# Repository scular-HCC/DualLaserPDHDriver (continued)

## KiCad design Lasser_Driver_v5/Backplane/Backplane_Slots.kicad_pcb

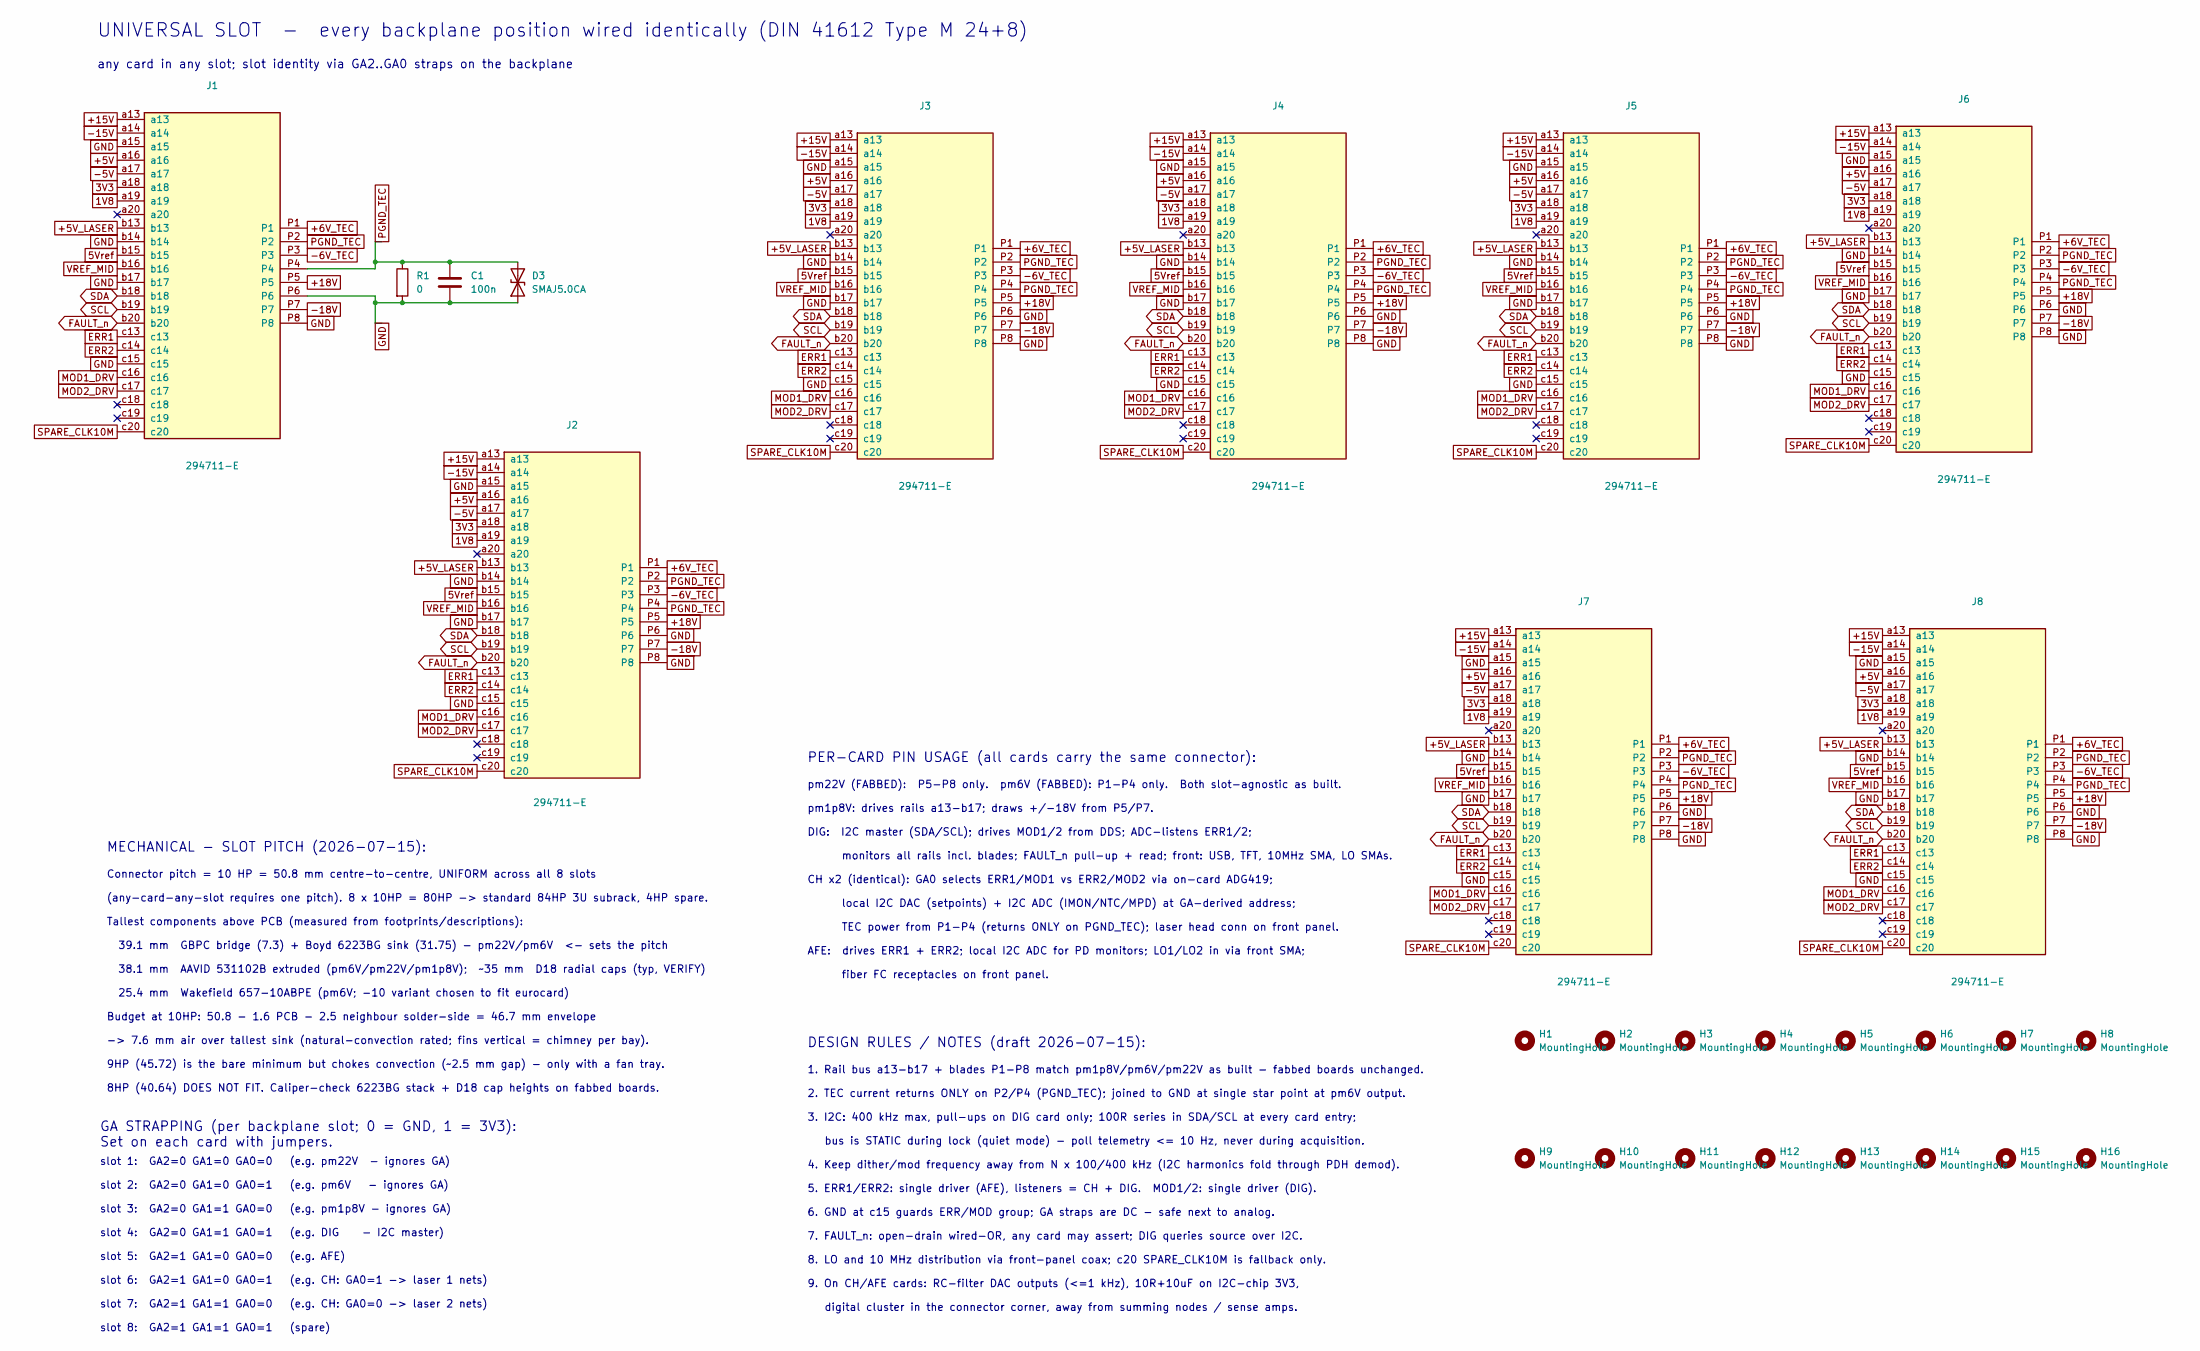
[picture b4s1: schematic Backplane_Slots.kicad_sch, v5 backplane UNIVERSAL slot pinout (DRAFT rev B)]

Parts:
C1: 100n; C_0805_2012Metric_Pad1.18x1.45mm_HandSolder
D3: SMAJ5.0CA; D_SMA-SMB_Universal_Handsoldering; MPN SMAJ5.0CA-E3/61
H1, H2, H3, H4, H5, H6, H7, H8, H9, H10, H11, H12, H13, H14, H15, H16: MountingHole; MountingHole_2.7mm
J1, J2, J3, J4, J5, J6, J7, J8: 294711-E; DIN41612_M_3x8+8_Female_Vertical_THT_Power
R1: 0; R_0805_2012Metric_Pad1.20x1.40mm_HandSolder

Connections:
1V8: J1.a19, J2.a19, J3.a19, J4.a19, J5.a19, J6.a19, J7.a19, J8.a19
3V3: J1.a18, J2.a18, J3.a18, J4.a18, J5.a18, J6.a18, J7.a18, J8.a18
5Vref: J1.b15, J2.b15, J3.b15, J4.b15, J5.b15, J6.b15, J7.b15, J8.b15
+5V: J1.a16, J2.a16, J3.a16, J4.a16, J5.a16, J6.a16, J7.a16, J8.a16
+5V_LASER: J1.b13, J2.b13, J3.b13, J4.b13, J5.b13, J6.b13, J7.b13, J8.b13
+6V_TEC: J1.P1, J2.P1, J3.P1, J4.P1, J5.P1, J6.P1, J7.P1, J8.P1
+15V: J1.a13, J2.a13, J3.a13, J4.a13, J5.a13, J6.a13, J7.a13, J8.a13
+18V: J1.P5, J2.P5, J3.P5, J4.P5, J5.P5, J6.P5, J7.P5, J8.P5
-5V: J1.a17, J2.a17, J3.a17, J4.a17, J5.a17, J6.a17, J7.a17, J8.a17
-6V_TEC: J1.P3, J2.P3, J3.P3, J4.P3, J5.P3, J6.P3, J7.P3, J8.P3
-15V: J1.a14, J2.a14, J3.a14, J4.a14, J5.a14, J6.a14, J7.a14, J8.a14
-18V: J1.P7, J2.P7, J3.P7, J4.P7, J5.P7, J6.P7, J7.P7, J8.P7
ERR1: J1.c13, J2.c13, J3.c13, J4.c13, J5.c13, J6.c13, J7.c13, J8.c13
ERR2: J1.c14, J2.c14, J3.c14, J4.c14, J5.c14, J6.c14, J7.c14, J8.c14
FAULT_n: J1.b20, J2.b20, J3.b20, J4.b20, J5.b20, J6.b20, J7.b20, J8.b20
GND: C1.2, D3.1 (A1), J1.P6, J1.P8, J1.a15, J1.b14, J1.b17, J1.c15, J2.P6, J2.P8, J2.a15, J2.b14, J2.b17, J2.c15, J3.P6, J3.P8, J3.a15, J3.b14, J3.b17, J3.c15, J4.P6, J4.P8, J4.a15, J4.b14, J4.b17, J4.c15, J5.P6, J5.P8, J5.a15, J5.b14, J5.b17, J5.c15, J6.P6, J6.P8, J6.a15, J6.b14, J6.b17, J6.c15, J7.P6, J7.P8, J7.a15, J7.b14, J7.b17, J7.c15, J8.P6, J8.P8, J8.a15, J8.b14, J8.b17, J8.c15, R1.2
MOD1_DRV: J1.c16, J2.c16, J3.c16, J4.c16, J5.c16, J6.c16, J7.c16, J8.c16
MOD2_DRV: J1.c17, J2.c17, J3.c17, J4.c17, J5.c17, J6.c17, J7.c17, J8.c17
PGND_TEC: C1.1, D3.2 (A2), J1.P2, J1.P4, J2.P2, J2.P4, J3.P2, J3.P4, J4.P2, J4.P4, J5.P2, J5.P4, J6.P2, J6.P4, J7.P2, J7.P4, J8.P2, J8.P4, R1.1
SCL: J1.b19, J2.b19, J3.b19, J4.b19, J5.b19, J6.b19, J7.b19, J8.b19
SDA: J1.b18, J2.b18, J3.b18, J4.b18, J5.b18, J6.b18, J7.b18, J8.b18
SPARE_CLK10M: J1.c20, J2.c20, J3.c20, J4.c20, J5.c20, J6.c20, J7.c20, J8.c20
VREF_MID: J1.b16, J2.b16, J3.b16, J4.b16, J5.b16, J6.b16, J7.b16, J8.b16

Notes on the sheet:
pm22V (FABBED): P5-P8 only. pm6V (FABBED): P1-P4 only. Both slot-agnostic as built.
DIG: I2C master (SDA/SCL); drives MOD1/2 from DDS; ADC-listens ERR1/2;
2. TEC current returns ONLY on P2/P4 (PGND_TEC); joined to GND at single star point at pm6V output.
8. LO and 10 MHz distribution via front-panel coax; c20 SPARE_CLK10M is fallback only.
AFE: drives ERR1 + ERR2; local I2C ADC for PD monitors; LO1/LO2 in via front SMA;
6. GND at c15 guards ERR/MOD group; GA straps are DC - safe next to analog.
38.1 mm AAVID 531102B extruded (pm6V/pm22V/pm1p8V); ~35 mm D18 radial caps (typ, VERIFY)
TEC power from P1-P4 (returns ONLY on PGND_TEC); laser head conn on front panel.
slot 5: GA2=1 GA1=0 GA0=0 (e.g. AFE)
slot 3: GA2=0 GA1=1 GA0=0 (e.g. pm1p8V - ignores GA)
PER-CARD PIN USAGE (all cards carry the same connector):
any card in any slot; slot identity via GA2..GA0 straps on the backplane
Budget at 10HP: 50.8 - 1.6 PCB - 2.5 neighbour solder-side = 46.7 mm envelope
(any-card-any-slot requires one pitch). 8 x 10HP = 80HP -> standard 84HP 3U subrack, 4HP spare.
1. Rail bus a13-b17 + blades P1-P8 match pm1p8V/pm6V/pm22V as built - fabbed boards unchanged.
slot 6: GA2=1 GA1=0 GA0=1 (e.g. CH: GA0=1 -> laser 1 nets)
slot 7: GA2=1 GA1=1 GA0=0 (e.g. CH: GA0=0 -> laser 2 nets)
bus is STATIC during lock (quiet mode) - poll telemetry <= 10 Hz, never during acquisition.
8HP (40.64) DOES NOT FIT. Caliper-check 6223BG stack + D18 cap heights on fabbed boards.
slot 4: GA2=0 GA1=1 GA0=1 (e.g. DIG - I2C master)
4. Keep dither/mod frequency away from N x 100/400 kHz (I2C harmonics fold through PDH demod).
slot 8: GA2=1 GA1=1 GA0=1 (spare)
Tallest components above PCB (measured from footprints/descriptions):
MECHANICAL - SLOT PITCH (2026-07-15):
GA STRAPPING (per backplane slot; 0 = GND, 1 = 3V3): Set on each card with jumpers.
local I2C DAC (setpoints) + I2C ADC (IMON/NTC/MPD) at GA-derived address;
39.1 mm GBPC bridge (7.3) + Boyd 6223BG sink (31.75) - pm22V/pm6V <- sets the pitch
DESIGN RULES / NOTES (draft 2026-07-15):
25.4 mm Wakefield 657-10ABPE (pm6V; -10 variant chosen to fit eurocard)
9. On CH/AFE cards: RC-filter DAC outputs (<=1 kHz), 10R+10uF on I2C-chip 3V3,
digital cluster in the connector corner, away from summing nodes / sense amps.
-> 7.6 mm air over tallest sink (natural-convection rated; fins vertical = chimney per bay).
7. FAULT_n: open-drain wired-OR, any card may assert; DIG queries source over I2C.
Connector pitch = 10 HP = 50.8 mm centre-to-centre, UNIFORM across all 8 slots
slot 2: GA2=0 GA1=0 GA0=1 (e.g. pm6V - ignores GA)
monitors all rails incl. blades; FAULT_n pull-up + read; front: USB, TFT, 10MHz SMA, LO SMAs.
CH x2 (identical): GA0 selects ERR1/MOD1 vs ERR2/MOD2 via on-card ADG419;
slot 1: GA2=0 GA1=0 GA0=0 (e.g. pm22V - ignores GA)
UNIVERSAL SLOT - every backplane position wired identically (DIN 41612 Type M 24+8)
fiber FC receptacles on front panel.

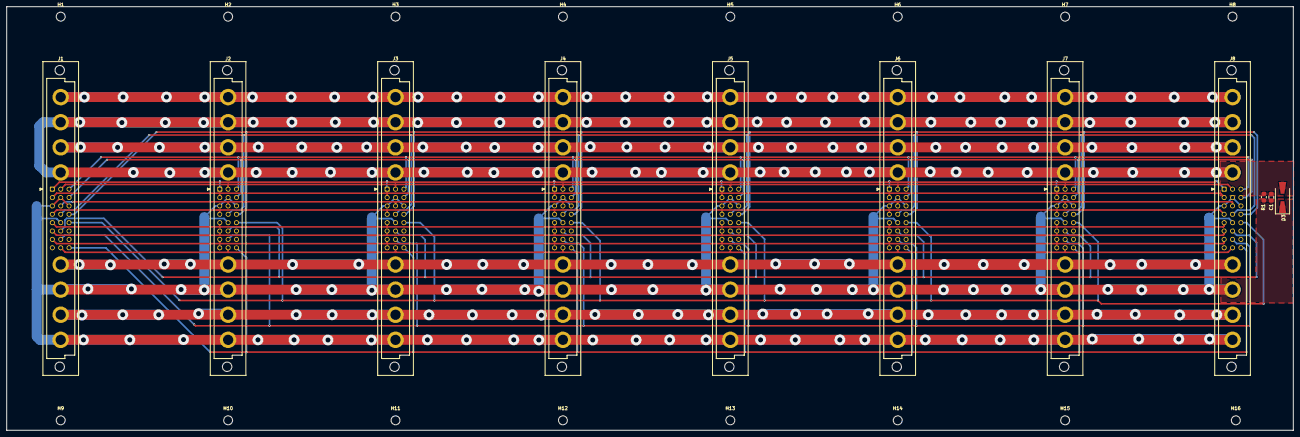
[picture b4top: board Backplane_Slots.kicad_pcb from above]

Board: 2 copper layers, 390.4 x 128.6 mm, 27 parts (0 on the bottom side), 23 nets.

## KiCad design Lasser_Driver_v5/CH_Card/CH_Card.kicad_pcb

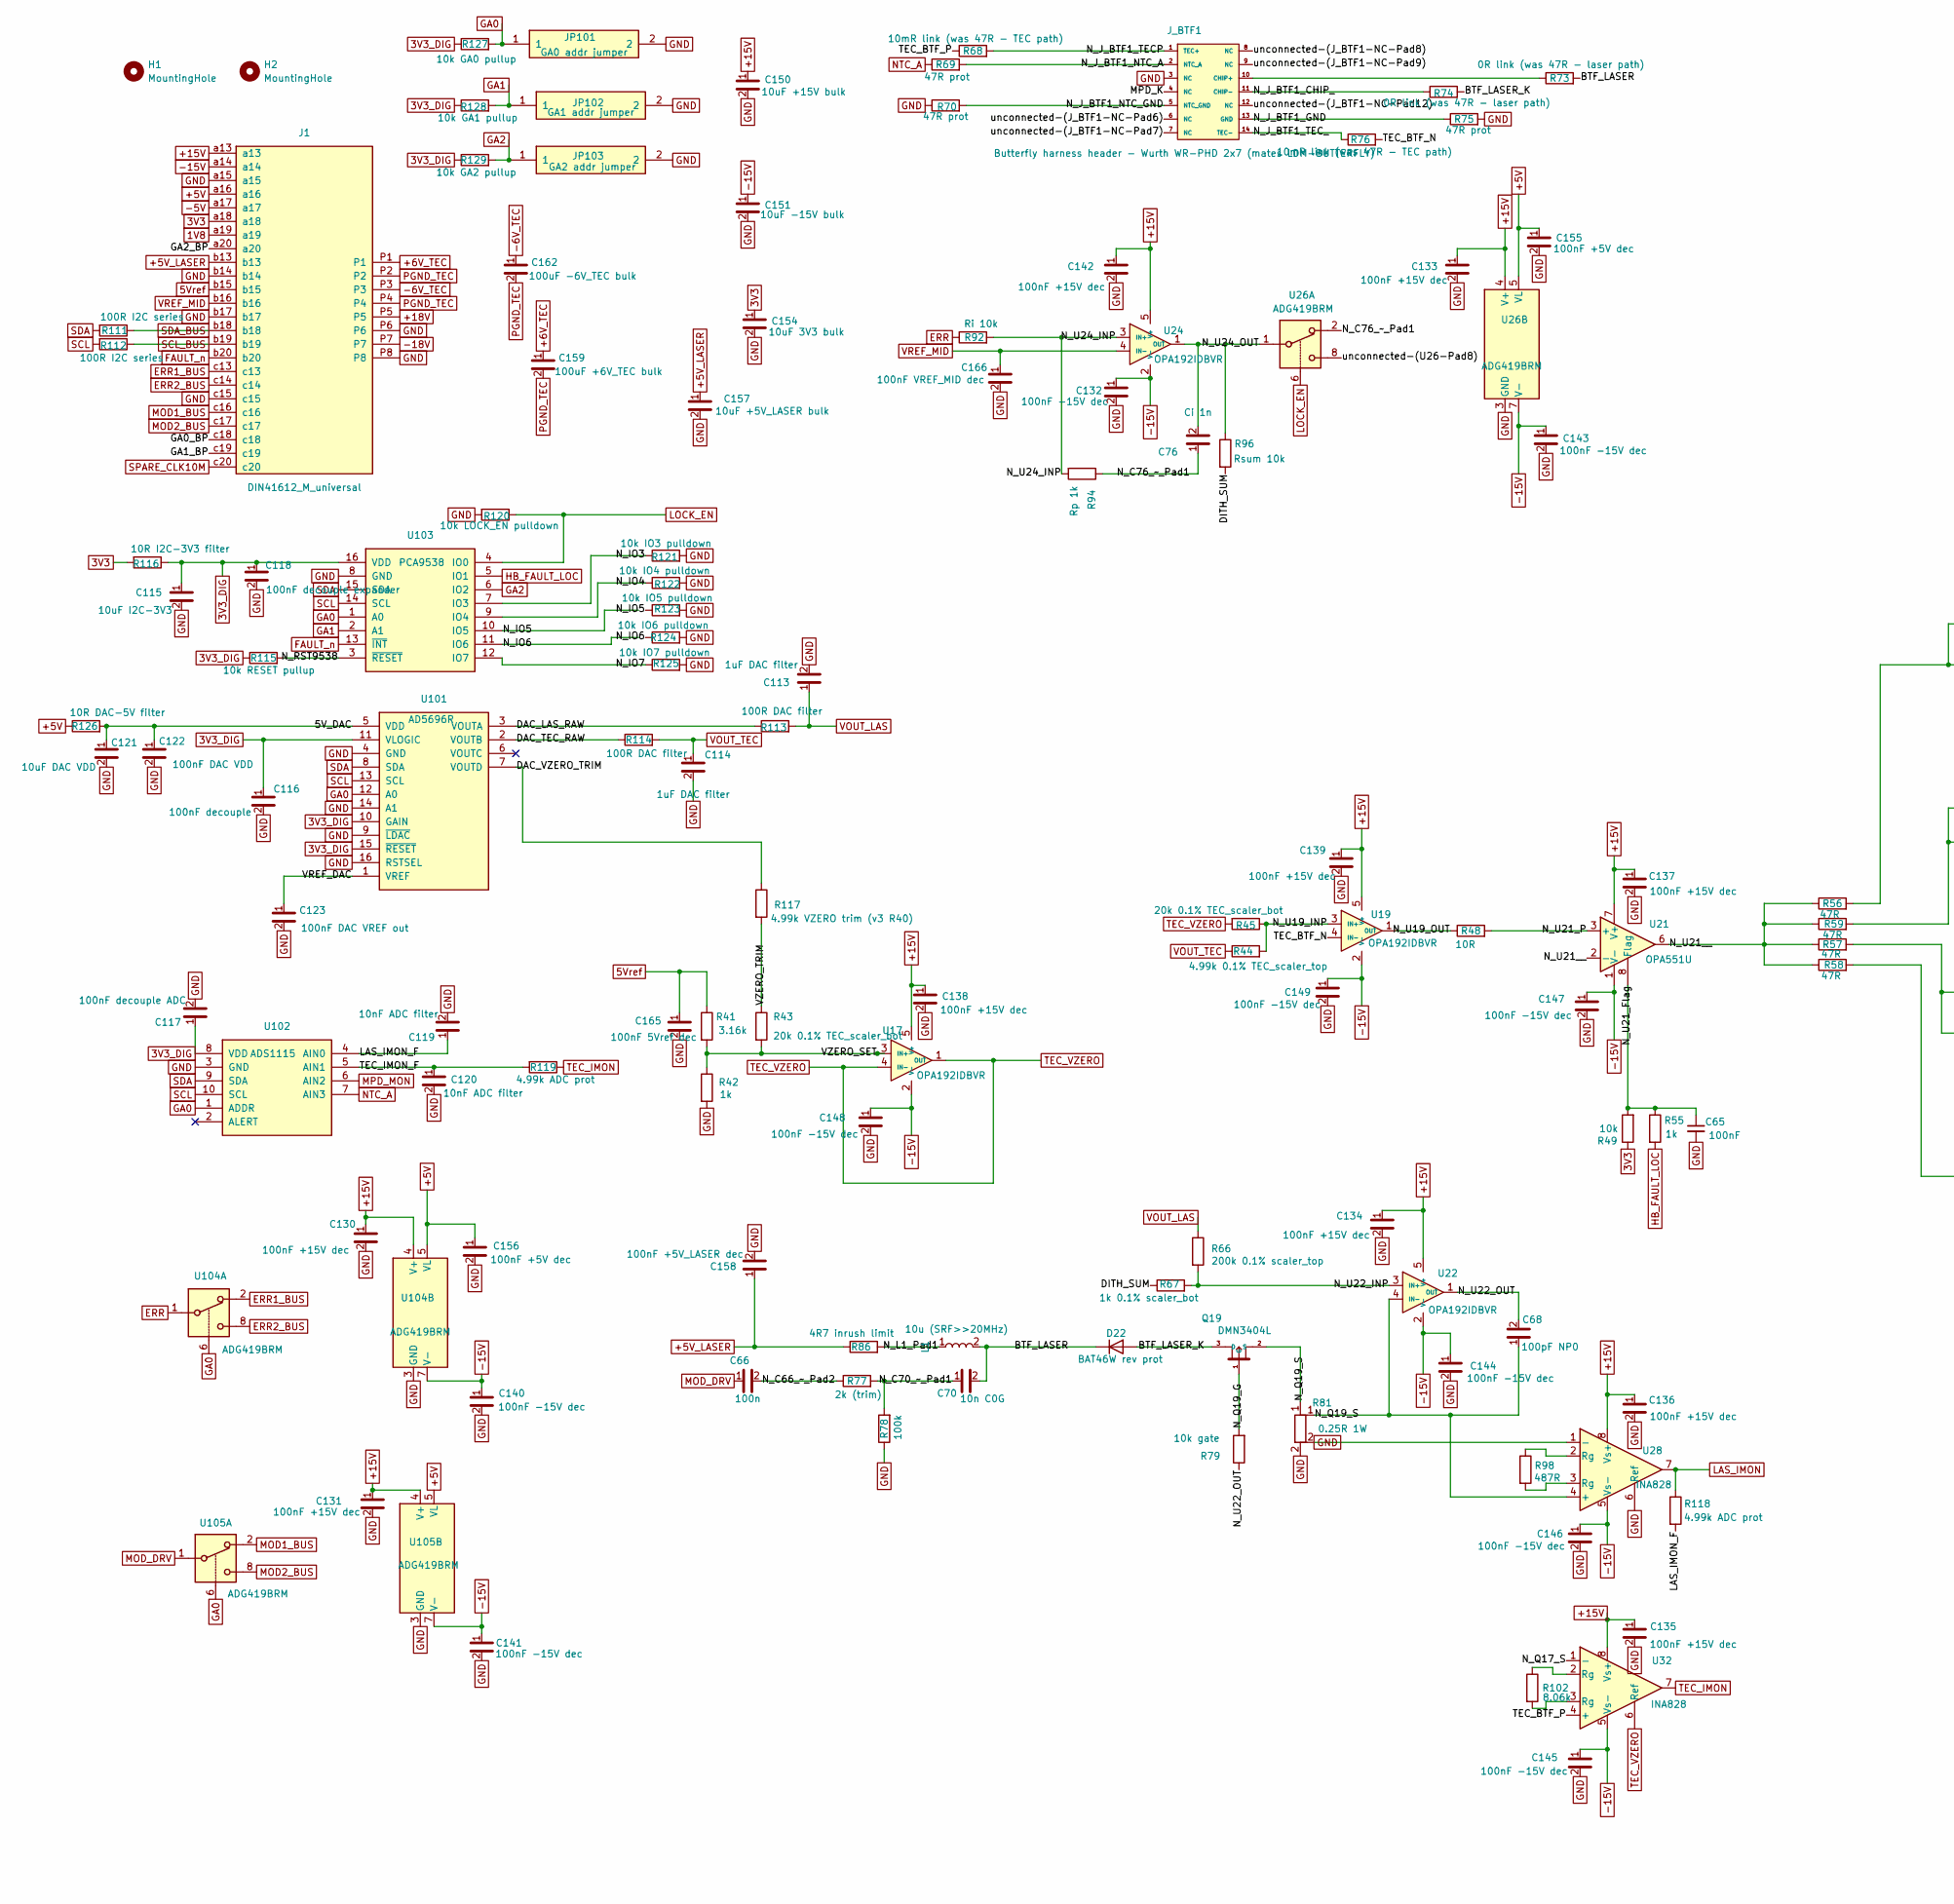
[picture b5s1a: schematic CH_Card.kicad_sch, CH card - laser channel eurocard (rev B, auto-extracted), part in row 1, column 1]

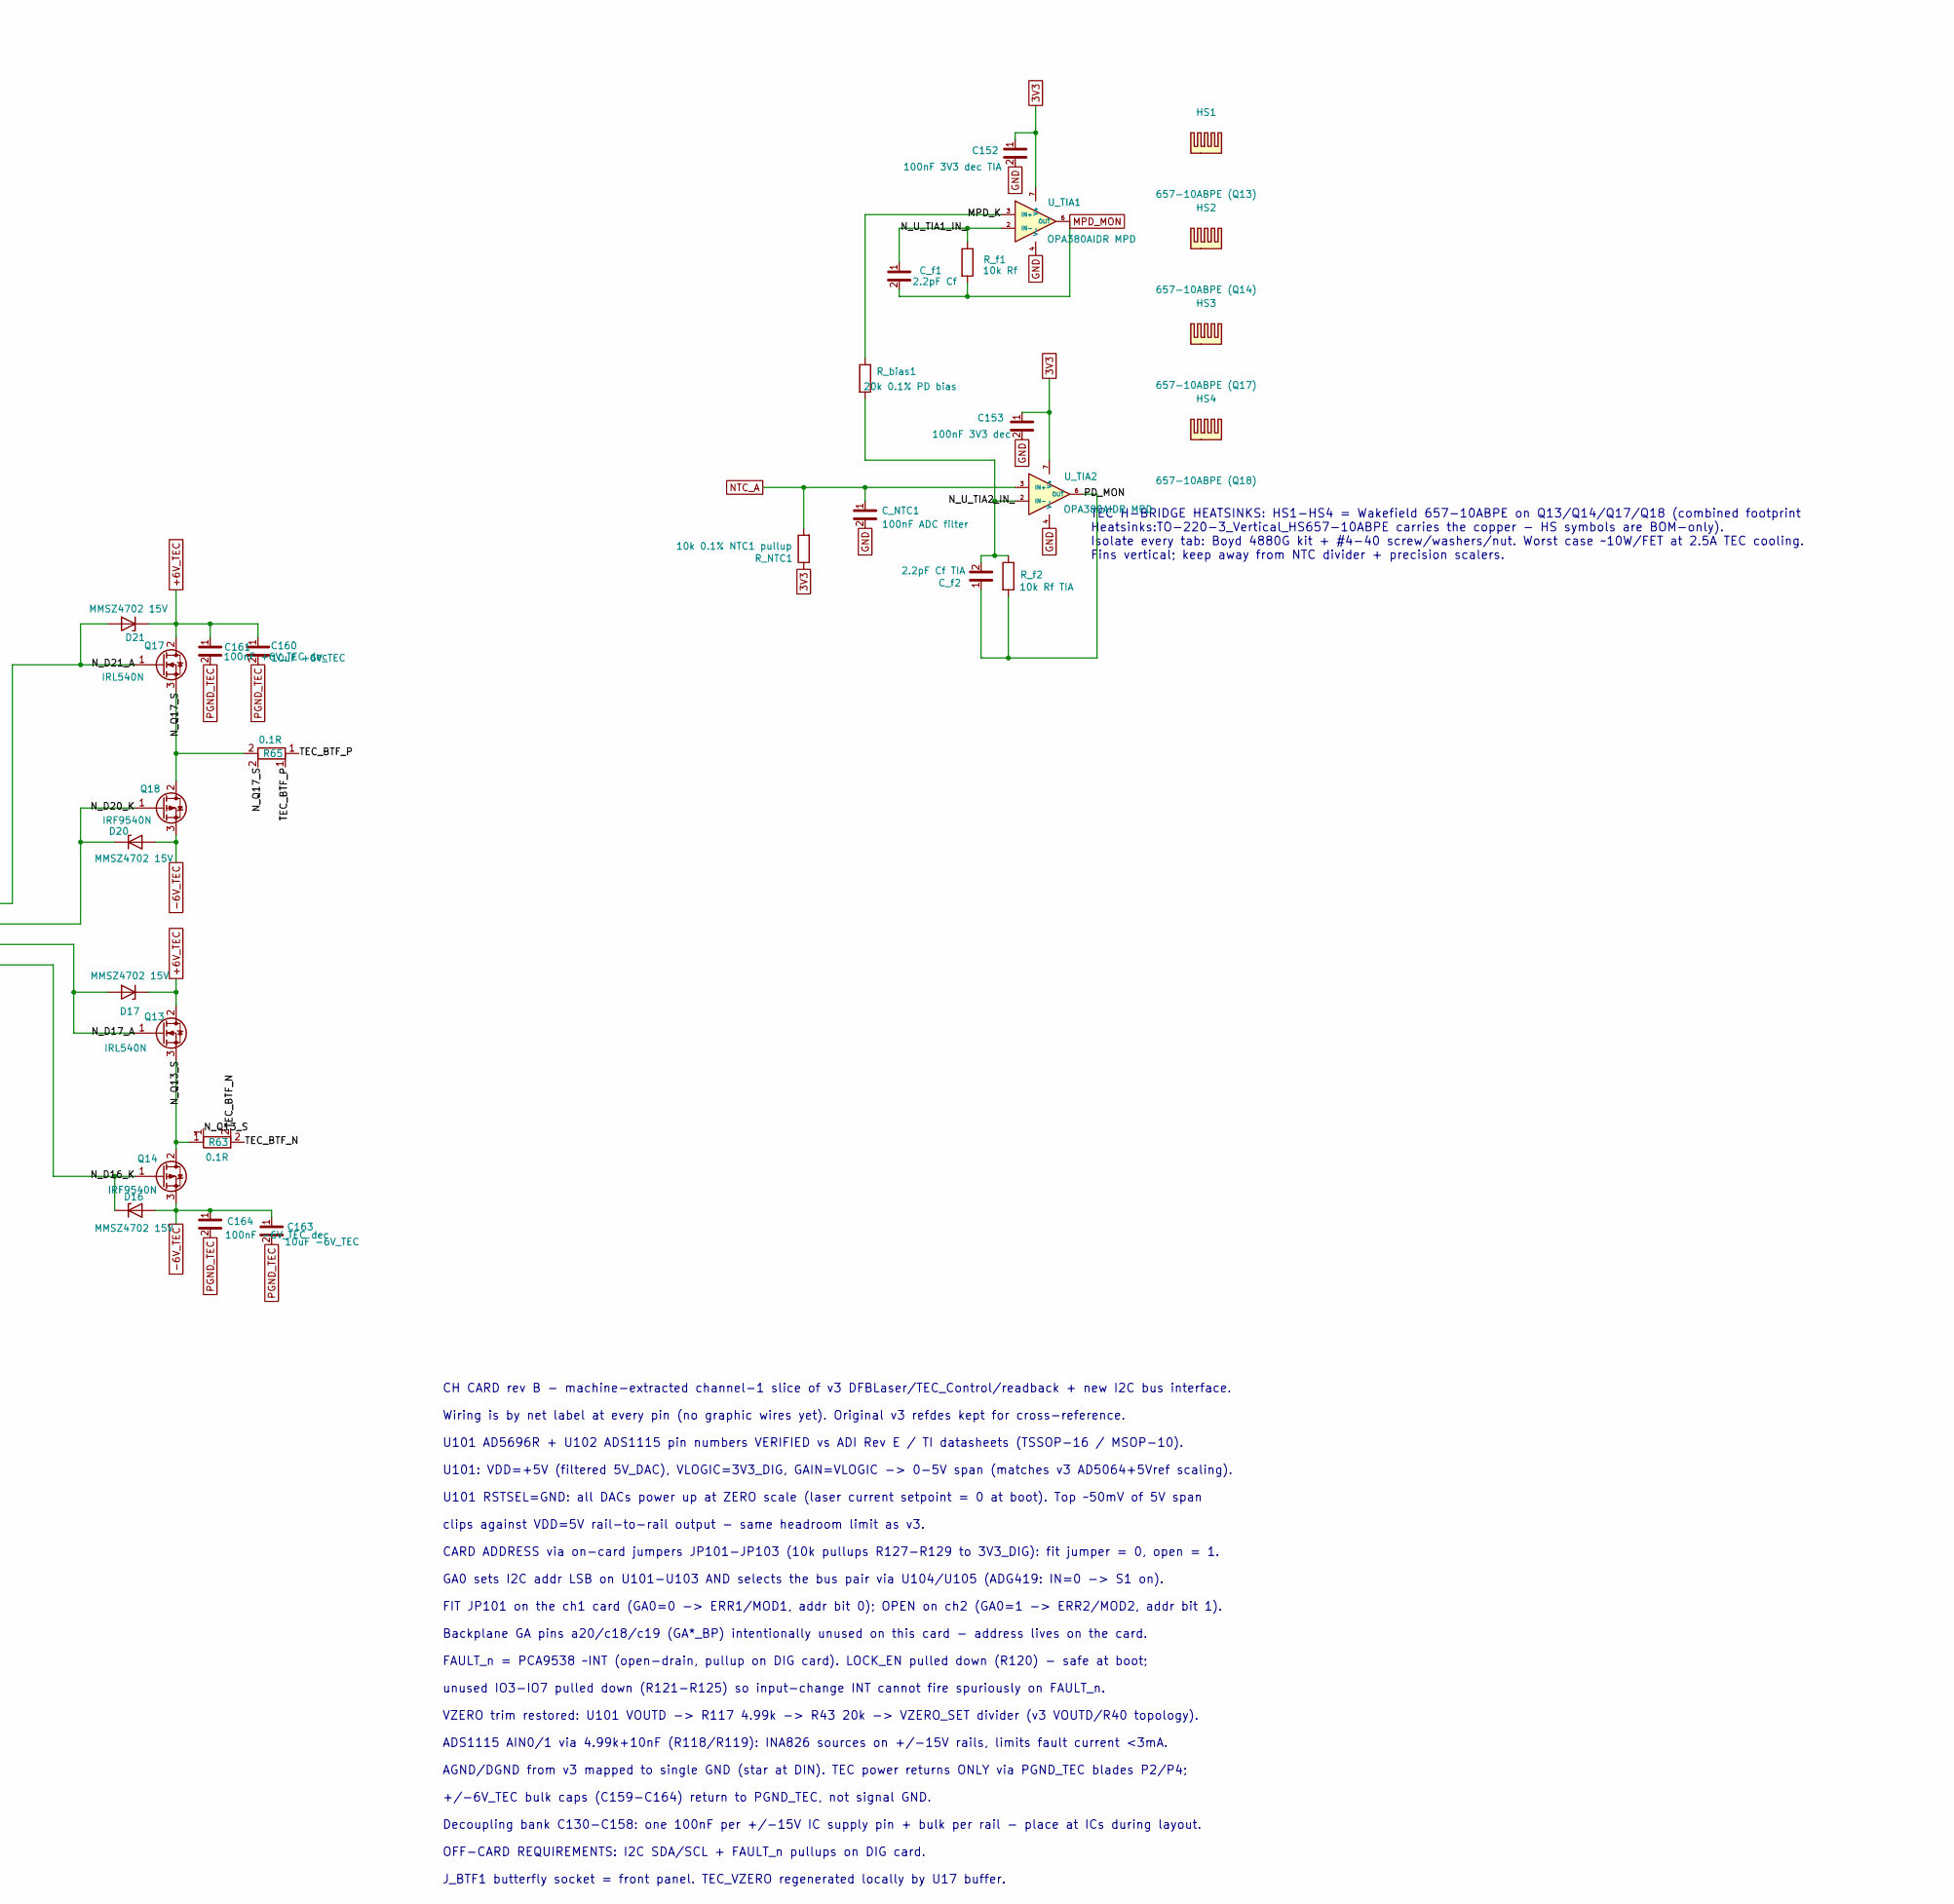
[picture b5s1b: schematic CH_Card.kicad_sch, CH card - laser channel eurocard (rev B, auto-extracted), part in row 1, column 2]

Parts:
C65: 100nF; C_0805_2012Metric_Pad1.18x1.45mm_HandSolder
C66: 100n; C_0805_2012Metric_Pad1.18x1.45mm_HandSolder
C68: 100pF NP0; C_0805_2012Metric_Pad1.18x1.45mm_HandSolder
C70: 10n C0G; C_0805_2012Metric_Pad1.18x1.45mm_HandSolder
C76: Ci 1n; C_0805_2012Metric_Pad1.18x1.45mm_HandSolder
C113, C114: 1uF DAC filter; C_0805_2012Metric_Pad1.18x1.45mm_HandSolder
C115: 10uF I2C-3V3; C_0805_2012Metric_Pad1.18x1.45mm_HandSolder
C116: 100nF decouple; C_0805_2012Metric_Pad1.18x1.45mm_HandSolder
C117: 100nF decouple ADC; C_0805_2012Metric_Pad1.18x1.45mm_HandSolder
C118: 100nF decouple expander; C_0805_2012Metric_Pad1.18x1.45mm_HandSolder
C119, C120: 10nF ADC filter; C_0805_2012Metric_Pad1.18x1.45mm_HandSolder
C121: 10uF DAC VDD; C_0805_2012Metric_Pad1.18x1.45mm_HandSolder
C122: 100nF DAC VDD; C_0805_2012Metric_Pad1.18x1.45mm_HandSolder
C123: 100nF DAC VREF out; C_0805_2012Metric_Pad1.18x1.45mm_HandSolder
C130, C131, C133, C134, C135, C136, C137, C138, C139, C142: 100nF +15V dec; C_0805_2012Metric_Pad1.18x1.45mm_HandSolder
C132, C140, C141, C143, C144, C145, C146, C147, C148, C149: 100nF -15V dec; C_0805_2012Metric_Pad1.18x1.45mm_HandSolder
C150: 10uF +15V bulk; C_0805_2012Metric_Pad1.18x1.45mm_HandSolder
C151: 10uF -15V bulk; C_0805_2012Metric_Pad1.18x1.45mm_HandSolder
C152: 100nF 3V3 dec TIA; C_0805_2012Metric_Pad1.18x1.45mm_HandSolder
C153: 100nF 3V3 dec; C_0805_2012Metric_Pad1.18x1.45mm_HandSolder
C154: 10uF 3V3 bulk; C_0805_2012Metric_Pad1.18x1.45mm_HandSolder
C155, C156: 100nF +5V dec; C_0805_2012Metric_Pad1.18x1.45mm_HandSolder
C157: 10uF +5V_LASER bulk; C_0805_2012Metric_Pad1.18x1.45mm_HandSolder
C158: 100nF +5V_LASER dec; C_0805_2012Metric_Pad1.18x1.45mm_HandSolder
C159: 100uF +6V_TEC bulk; C_1210_3225Metric
C160: 10uF +6V_TEC; C_0805_2012Metric_Pad1.18x1.45mm_HandSolder
C161: 100nF +6V_TEC dec; C_0805_2012Metric_Pad1.18x1.45mm_HandSolder
C162: 100uF -6V_TEC bulk; C_1210_3225Metric
C163: 10uF -6V_TEC; C_0805_2012Metric_Pad1.18x1.45mm_HandSolder
C164: 100nF -6V_TEC dec; C_0805_2012Metric_Pad1.18x1.45mm_HandSolder
C165: 100nF 5Vref dec; C_0805_2012Metric_Pad1.18x1.45mm_HandSolder
C166: 100nF VREF_MID dec; C_0805_2012Metric_Pad1.18x1.45mm_HandSolder
C_NTC1: 100nF ADC filter; C_0805_2012Metric_Pad1.18x1.45mm_HandSolder
C_f1: 2.2pF Cf; C_0402_1005Metric
C_f2: 2.2pF Cf TIA; C_0402_1005Metric
D16, D17, D20, D21: MMSZ4702 15V; D_SOD-123
D22: BAT46W rev prot; D_SOD-123
H1, H2: MountingHole; MountingHole_2.7mm
HS1: 657-10ABPE (Q13)
HS2: 657-10ABPE (Q14)
HS3: 657-10ABPE (Q17)
HS4: 657-10ABPE (Q18)
J1: DIN41612_M_universal; DIN41612_M_3x8+8_Male_Horizontal_THT_Power
JP101: GA0 addr jumper; PinHeader_1x02_P2.54mm_Vertical
JP102: GA1 addr jumper; PinHeader_1x02_P2.54mm_Vertical
JP103: GA2 addr jumper; PinHeader_1x02_P2.54mm_Vertical
J_BTF1: Butterfly harness header - Wurth WR-PHD 2x7 (mate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; PinHeader_2x07_P2.54mm_Vertical
L1: 10u (SRF>>20MHz); L_1812_4532Metric_Pad1.30x3.40mm_HandSolder
Q13, Q17: IRL540N; TO-220-3_Vertical_HS657-10ABPE
Q14, Q18: IRF9540N; TO-220-3_Vertical_HS657-10ABPE
Q19: DMN3404L; SOT-23
R41: 3.16k; R_0805_2012Metric_Pad1.20x1.40mm_HandSolder
R42, R55: 1k; R_0805_2012Metric_Pad1.20x1.40mm_HandSolder
R43, R45: 20k 0.1% TEC_scaler_bot; R_0805_2012Metric
R44: 4.99k 0.1% TEC_scaler_top; R_0805_2012Metric
R48: 10R; R_0805_2012Metric_Pad1.20x1.40mm_HandSolder
R49: 10k; R_0805_2012Metric_Pad1.20x1.40mm_HandSolder
R56, R57, R58, R59: 47R; R_0805_2012Metric_Pad1.20x1.40mm_HandSolder
R63, R65: 0.1R; R_2512_6332Metric
R66: 200k 0.1% scaler_top; R_0805_2012Metric
R67: 1k 0.1% scaler_bot; R_0805_2012Metric
R68, R76: 10mR link (was 47R - TEC path); R_2512_6332Metric
R69, R70, R75: 47R prot; R_0805_2012Metric_Pad1.20x1.40mm_HandSolder
R73, R74: 0R link (was 47R - laser path); R_0805_2012Metric_Pad1.20x1.40mm_HandSolder
R77: 2k (trim); R_0805_2012Metric_Pad1.20x1.40mm_HandSolder
R78: 100k; R_0805_2012Metric_Pad1.20x1.40mm_HandSolder
R79: 10k gate; R_0805_2012Metric_Pad1.20x1.40mm_HandSolder
R81: 0.25R 1W; R_2512_6332Metric
R86: 4R7 inrush limit; R_2512_6332Metric
R92: Ri 10k; R_0805_2012Metric_Pad1.20x1.40mm_HandSolder
R94: Rp 1k; R_0805_2012Metric_Pad1.20x1.40mm_HandSolder
R96: Rsum 10k; R_0805_2012Metric_Pad1.20x1.40mm_HandSolder
R98: 487R; R_0805_2012Metric_Pad1.20x1.40mm_HandSolder
R102: 8.06k; R_0805_2012Metric_Pad1.20x1.40mm_HandSolder
R111, R112: 100R I2C series; R_0805_2012Metric_Pad1.20x1.40mm_HandSolder
R113, R114: 100R DAC filter; R_0805_2012Metric_Pad1.20x1.40mm_HandSolder
R115: 10k RESET pullup; R_0805_2012Metric_Pad1.20x1.40mm_HandSolder
R116: 10R I2C-3V3 filter; R_0805_2012Metric_Pad1.20x1.40mm_HandSolder
R117: 4.99k VZERO trim (v3 R40); R_0805_2012Metric_Pad1.20x1.40mm_HandSolder
R118, R119: 4.99k ADC prot; R_0805_2012Metric_Pad1.20x1.40mm_HandSolder
R120: 10k LOCK_EN pulldown; R_0805_2012Metric_Pad1.20x1.40mm_HandSolder
R121: 10k IO3 pulldown; R_0805_2012Metric_Pad1.20x1.40mm_HandSolder
R122: 10k IO4 pulldown; R_0805_2012Metric_Pad1.20x1.40mm_HandSolder
R123: 10k IO5 pulldown; R_0805_2012Metric_Pad1.20x1.40mm_HandSolder
R124: 10k IO6 pulldown; R_0805_2012Metric_Pad1.20x1.40mm_HandSolder
R125: 10k IO7 pulldown; R_0805_2012Metric_Pad1.20x1.40mm_HandSolder
R126: 10R DAC-5V filter; R_0805_2012Metric_Pad1.20x1.40mm_HandSolder
R127: 10k GA0 pullup; R_0805_2012Metric_Pad1.20x1.40mm_HandSolder
R128: 10k GA1 pullup; R_0805_2012Metric_Pad1.20x1.40mm_HandSolder
R129: 10k GA2 pullup; R_0805_2012Metric_Pad1.20x1.40mm_HandSolder
R_NTC1: 10k 0.1% NTC1 pullup; R_0805_2012Metric
R_bias1: 20k 0.1% PD bias; R_0805_2012Metric
R_f1: 10k Rf; R_0805_2012Metric_Pad1.20x1.40mm_HandSolder
R_f2: 10k Rf TIA; R_0805_2012Metric_Pad1.20x1.40mm_HandSolder
U17, U19, U22, U24: OPA192IDBVR; SOT-23-5
U21: OPA551U; SOIC-8_3.9x4.9mm_P1.27mm
U26, U104, U105: ADG419BRM; MSOP-8_3x3mm_P0.65mm
U28, U32: INA828; SOIC-8_3.9x4.9mm_P1.27mm
U101: AD5696R; TSSOP-16_4.4x5mm_P0.65mm
U102: ADS1115; MSOP-10_3x3mm_P0.5mm
U103: PCA9538; TSSOP-16_4.4x5mm_P0.65mm
U_TIA1, U_TIA2: OPA380AIDR MPD; SOIC-8_3.9x4.9mm_P1.27mm

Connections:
1V8: J1.a19
3V3: C152.1, C153.1, C154.1, J1.a18, R49.1, R116.2, R_NTC1.1, U_TIA1.7 (V+), U_TIA2.7 (V+)
3V3_DIG: C115.1, C116.1, C117.1, C118.1, R115.1, R116.1, R127.1, R128.1, R129.1, U101.10 (GAIN), U101.11 (VLOGIC), U101.15 (~RESET), U102.8 (VDD), U103.16 (VDD)
5Vref: C165.1, J1.b15, R41.1
+5V: C155.1, C156.1, J1.a16, R126.1, U26.5 (VL), U104.5 (VL), U105.5 (VL)
+5V_LASER: C157.1, C158.1, J1.b13, R86.1
+6V_TEC: C159.1, C160.1, C161.1, D17.1 (K), D21.1 (K), J1.P1, Q13.2 (D), Q17.2 (D)
+15V: C130.1, C131.1, C133.1, C134.1, C135.1, C136.1, C137.1, C138.1, C139.1, C142.1, C150.1, J1.a13, U17.5 (V+), U19.5 (V+), U21.7 (V+), U22.5 (V+), U24.5 (V+), U26.4 (V+), U28.8 (Vs+), U32.8 (Vs+), U104.4 (V+), U105.4 (V+)
+18V: J1.P5
-5V: J1.a17
-6V_TEC: C162.1, C163.1, C164.1, D16.2 (A), D20.2 (A), J1.P3, Q14.3 (S), Q18.3 (S)
-15V: C132.1, C140.1, C141.1, C143.1, C144.1, C145.1, C146.1, C147.1, C148.1, C149.1, C151.1, J1.a14, U17.2 (V-), U19.2 (V-), U21.1 (V-), U21.4 (V-), U21.5 (V-), U22.2 (V-), U24.2 (V-), U26.7 (V-), U28.5 (Vs-), U32.5 (Vs-), U104.7 (V-), U105.7 (V-)
-18V: J1.P7
/5V_DAC: C121.1, C122.1, R126.2, U101.5 (VDD)
/BTF_LASER: C70.2, D22.1 (K), L1.2, R73.2
/BTF_LASER_K: D22.2 (A), Q19.3 (D), R74.2
/DAC_LAS_RAW: R113.1, U101.3 (VOUTA)
/DAC_TEC_RAW: R114.1, U101.2 (VOUTB)
/DAC_VZERO_TRIM: R117.1, U101.7 (VOUTD)
/DITH_SUM: R67.1, R96.2
/GA0_BP: J1.c18
/GA1_BP: J1.c19
/GA2_BP: J1.a20
/LAS_IMON_F: C119.1, R118.2, U102.4 (AIN0)
/MPD_K: J_BTF1.4 (NC), R_bias1.1, U_TIA1.3 (IN+)
/N_C66_~_Pad2: C66.2, R77.1
/N_C70_~_Pad1: C70.1, R77.2, R78.2
/N_C76_~_Pad1: C76.1, R94.1, U26.2
/N_D16_K: D16.1 (K), Q14.1 (G), R58.2
/N_D17_A: D17.2 (A), Q13.1 (G), R57.2
/N_D20_K: D20.1 (K), Q18.1 (G), R59.2
/N_D21_A: D21.2 (A), Q17.1 (G), R56.2
/N_IO3: R121.1, U103.7 (IO3)
/N_IO4: R122.1, U103.9 (IO4)
/N_IO5: R123.1, U103.10 (IO5)
/N_IO6: R124.1, U103.11 (IO6)
/N_IO7: R125.1, U103.12 (IO7)
/N_J_BTF1_CHIP_: J_BTF1.11 (CHIP-), R74.1
/N_J_BTF1_GND: J_BTF1.13 (GND), R75.1
/N_J_BTF1_NTC_A: J_BTF1.2 (NTC_A), R69.2
/N_J_BTF1_NTC_GND: J_BTF1.5 (NTC_GND), R70.2
/N_J_BTF1_TECP: J_BTF1.1 (TEC+), R68.2
/N_J_BTF1_TEC_: J_BTF1.14 (TEC-), R76.1
/N_L1_Pad1: L1.1, R86.2
/N_Q13_S: Q13.3 (S), Q14.2 (D), R63.1
/N_Q17_S: Q17.3 (S), Q18.2 (D), R65.2, U32.1 (-)
/N_Q19_G: Q19.1 (G), R79.2
/N_Q19_S: C68.1, Q19.2 (S), R81.1, U22.4 (IN-), U28.4 (+)
/N_RST9538: R115.2, U103.3 (~RESET)
/N_U19_INP: R44.2, R45.1, U19.3 (IN+)
/N_U19_OUT: R48.1, U19.1 (OUT)
/N_U21_Flag: C65.1, R49.2, R55.1, U21.8 (Flag)
/N_U21_P: R48.2, U21.3 (+)
/N_U21__: R56.1, R57.1, R58.1, R59.1, U21.2 (-), U21.6
/N_U22_INP: R66.2, R67.2, U22.3 (IN+)
/N_U22_OUT: C68.2, R79.1, U22.1 (OUT)
/N_U24_INP: R92.2, R94.2, U24.3 (IN+)
/N_U24_OUT: C76.2, R96.1, U24.1 (OUT), U26.1
/N_U_TIA1_IN_: C_f1.1, R_f1.1, U_TIA1.2 (IN-)
/N_U_TIA2_IN_: C_f2.2, R_bias1.2, R_f2.1, U_TIA2.2 (IN-)
/PD_MON: C_f2.1, R_f2.2, U_TIA2.6 (OUT)
/TEC_BTF_N: R63.2, R76.2, U19.4 (IN-)
/TEC_BTF_P: R65.1, R68.1, U32.4 (+)
/TEC_IMON_F: C120.1, R119.2, U102.5 (AIN1)
/VREF_DAC: C123.1, U101.1 (VREF)
/VZERO_SET: R41.2, R42.1, R43.2, U17.3 (IN+)
/VZERO_TRIM: R43.1, R117.2
/unconnected-(J_BTF1-NC-Pad6): J_BTF1.6 (NC)
/unconnected-(J_BTF1-NC-Pad7): J_BTF1.7 (NC)
/unconnected-(J_BTF1-NC-Pad8): J_BTF1.8 (NC)
/unconnected-(J_BTF1-NC-Pad9): J_BTF1.9 (NC)
/unconnected-(J_BTF1-NC-Pad12): J_BTF1.12 (NC)
/unconnected-(U26-Pad8): U26.8
ERR: R92.1, U104.1
ERR1_BUS: J1.c13, U104.2
ERR2_BUS: J1.c14, U104.8
FAULT_n: J1.b20, U103.13 (~INT)
GA0: JP101.1, R127.2, U101.12 (A0), U102.1 (ADDR), U103.1 (A0), U104.6, U105.6
GA1: JP102.1, R128.2, U103.2 (A1)
GA2: JP103.1, R129.2, U103.6 (IO2)
GND: C65.2, C113.2, C114.2, C115.2, C116.2, C117.2, C118.2, C119.2, C120.2, C121.2, C122.2, C123.2, C130.2, C131.2, C132.2, C133.2, C134.2, C135.2, C136.2, C137.2, C138.2, C139.2, C140.2, C141.2, C142.2, C143.2, C144.2, C145.2, C146.2, C147.2, C148.2, C149.2, C150.2, C151.2, C152.2, C153.2, C154.2, C155.2, C156.2, C157.2, C158.2, C165.2, C166.2, C_NTC1.2, J1.P6, J1.P8, J1.a15, J1.b14, J1.b17, J1.c15, JP101.2, JP102.2, JP103.2, J_BTF1.3 (NC), R42.2, R70.1, R75.2, R78.1, R81.2, R120.2, R121.2, R122.2, R123.2, R124.2, R125.2, U26.3 (GND), U28.1 (-), U28.6 (Ref), U101.4 (GND), U101.9 (~LDAC), U101.14 (A1), U101.16 (RSTSEL), U102.3 (GND), U103.8 (GND), U104.3 (GND), U105.3 (GND), U_TIA1.4 (V-), U_TIA2.4 (V-)
HB_FAULT_LOC: R55.2, U103.5 (IO1)
LAS_IMON: R118.1, U28.7
LOCK_EN: R120.1, U26.6, U103.4 (IO0)
MOD1_BUS: J1.c16, U105.2
MOD2_BUS: J1.c17, U105.8
MOD_DRV: C66.1, U105.1
MPD_MON: C_f1.2, R_f1.2, U102.6 (AIN2), U_TIA1.6 (OUT)
NTC_A: C_NTC1.1, R69.1, R_NTC1.2, U102.7 (AIN3), U_TIA2.3 (IN+)
unnamed: J_BTF1.10 (CHIP+), R73.1
unnamed: R98.1, U28.2 (Rg)
unnamed: R98.2, U28.3 (Rg)
unnamed: R102.1, U32.2 (Rg)
unnamed: R102.2, U32.3 (Rg)
PGND_TEC: C159.2, C160.2, C161.2, C162.2, C163.2, C164.2, J1.P2, J1.P4
SCL: R112.2, U101.13 (SCL), U102.10 (SCL), U103.14 (SCL)
SCL_BUS: J1.b19, R112.1
SDA: R111.2, U101.8 (SDA), U102.9 (SDA), U103.15 (SDA)
SDA_BUS: J1.b18, R111.1
SPARE_CLK10M: J1.c20
TEC_IMON: R119.1, U32.7
TEC_VZERO: R45.2, U17.1 (OUT), U17.4 (IN-), U32.6 (Ref)
VOUT_LAS: C113.1, R66.1, R113.2
VOUT_TEC: C114.1, R44.1, R114.2
VREF_MID: C166.1, J1.b16, U24.4 (IN-)

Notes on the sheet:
ADS1115 AIN0/1 via 4.99k+10nF (R118/R119): INA826 sources on +/-15V rails, limits fault current <3mA.
Backplane GA pins a20/c18/c19 (GA*_BP) intentionally unused on this card - address lives on the card.
J_BTF1 butterfly socket = front panel. TEC_VZERO regenerated locally by U17 buffer.
Wiring is by net label at every pin (no graphic wires yet). Original v3 refdes kept for cross-reference.
VZERO trim restored: U101 VOUTD -> R117 4.99k -> R43 20k -> VZERO_SET divider (v3 VOUTD/R40 topology).
AGND/DGND from v3 mapped to single GND (star at DIN). TEC power returns ONLY via PGND_TEC blades P2/P4;
unused IO3-IO7 pulled down (R121-R125) so input-change INT cannot fire spuriously on FAULT_n.
+/-6V_TEC bulk caps (C159-C164) return to PGND_TEC, not signal GND.
FIT JP101 on the ch1 card (GA0=0 -> ERR1/MOD1, addr bit 0); OPEN on ch2 (GA0=1 -> ERR2/MOD2, addr bit 1).
U101 RSTSEL=GND: all DACs power up at ZERO scale (laser current setpoint = 0 at boot). Top ~50mV of 5V span
CH CARD rev B - machine-extracted channel-1 slice of v3 DFBLaser/TEC_Control/readback + new I2C bus interface.
CARD ADDRESS via on-card jumpers JP101-JP103 (10k pullups R127-R129 to 3V3_DIG): fit jumper = 0, open = 1.
U101 AD5696R + U102 ADS1115 pin numbers VERIFIED vs ADI Rev E / TI datasheets (TSSOP-16 / MSOP-10).
GA0 sets I2C addr LSB on U101-U103 AND selects the bus pair via U104/U105 (ADG419: IN=0 -> S1 on).
U101: VDD=+5V (filtered 5V_DAC), VLOGIC=3V3_DIG, GAIN=VLOGIC -> 0-5V span (matches v3 AD5064+5Vref scaling).
clips against VDD=5V rail-to-rail output - same headroom limit as v3.
Decoupling bank C130-C158: one 100nF per +/-15V IC supply pin + bulk per rail - place at ICs during layout.
OFF-CARD REQUIREMENTS: I2C SDA/SCL + FAULT_n pullups on DIG card.
FAULT_n = PCA9538 ~INT (open-drain, pullup on DIG card). LOCK_EN pulled down (R120) - safe at boot;
TEC H-BRIDGE HEATSINKS: HS1-HS4 = Wakefield 657-10ABPE on Q13/Q14/Q17/Q18 (combined footprint Heatsinks:TO-220-3_Vertical_HS657-10ABPE carries the copper - HS symbols are BOM-only). Isolate every tab: Boyd 4880G kit + #4-40 screw/washers/nut. Worst case ~10W/FET at 2.5A TEC cooling. Fins vertical; 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

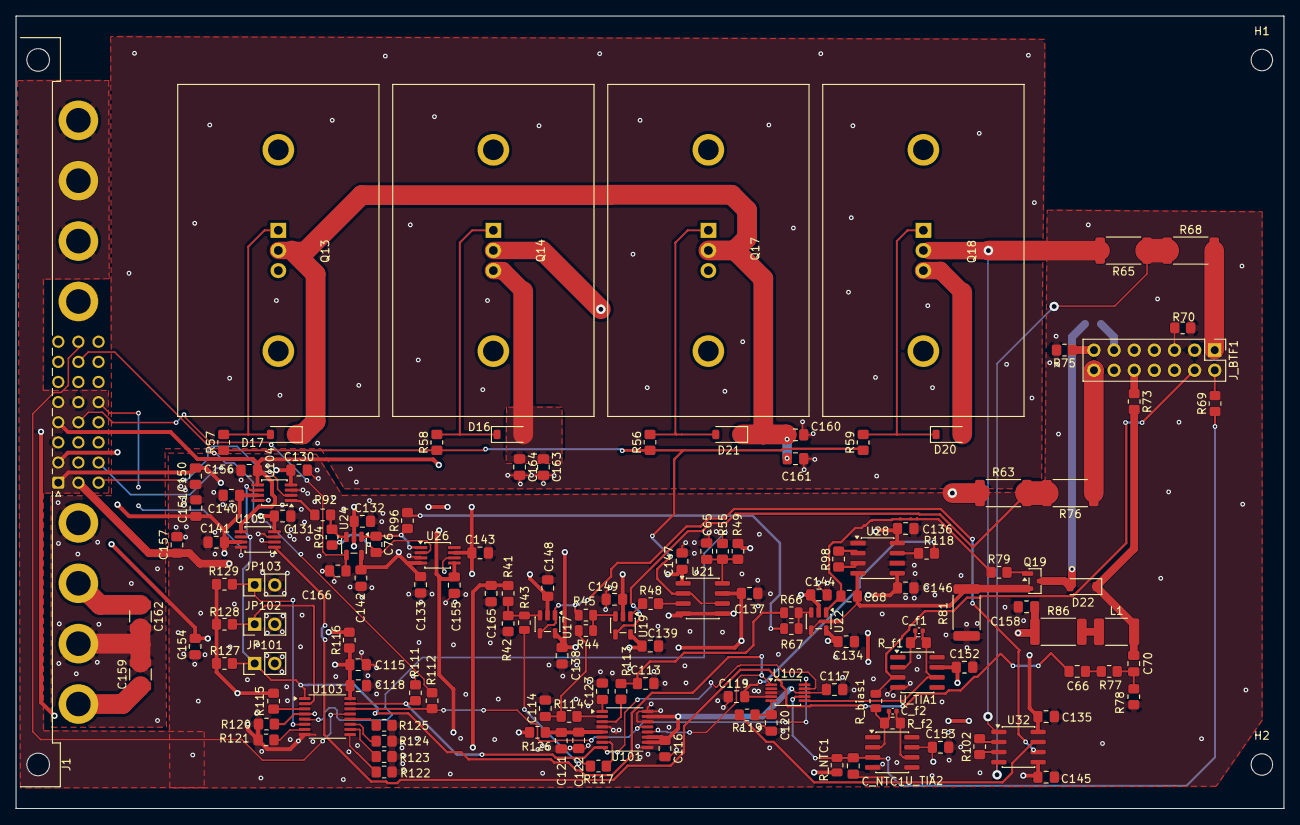
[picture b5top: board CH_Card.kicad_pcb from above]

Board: 6 copper layers, 160.0 x 100.0 mm, 145 parts (1 on the bottom side), 91 nets.
